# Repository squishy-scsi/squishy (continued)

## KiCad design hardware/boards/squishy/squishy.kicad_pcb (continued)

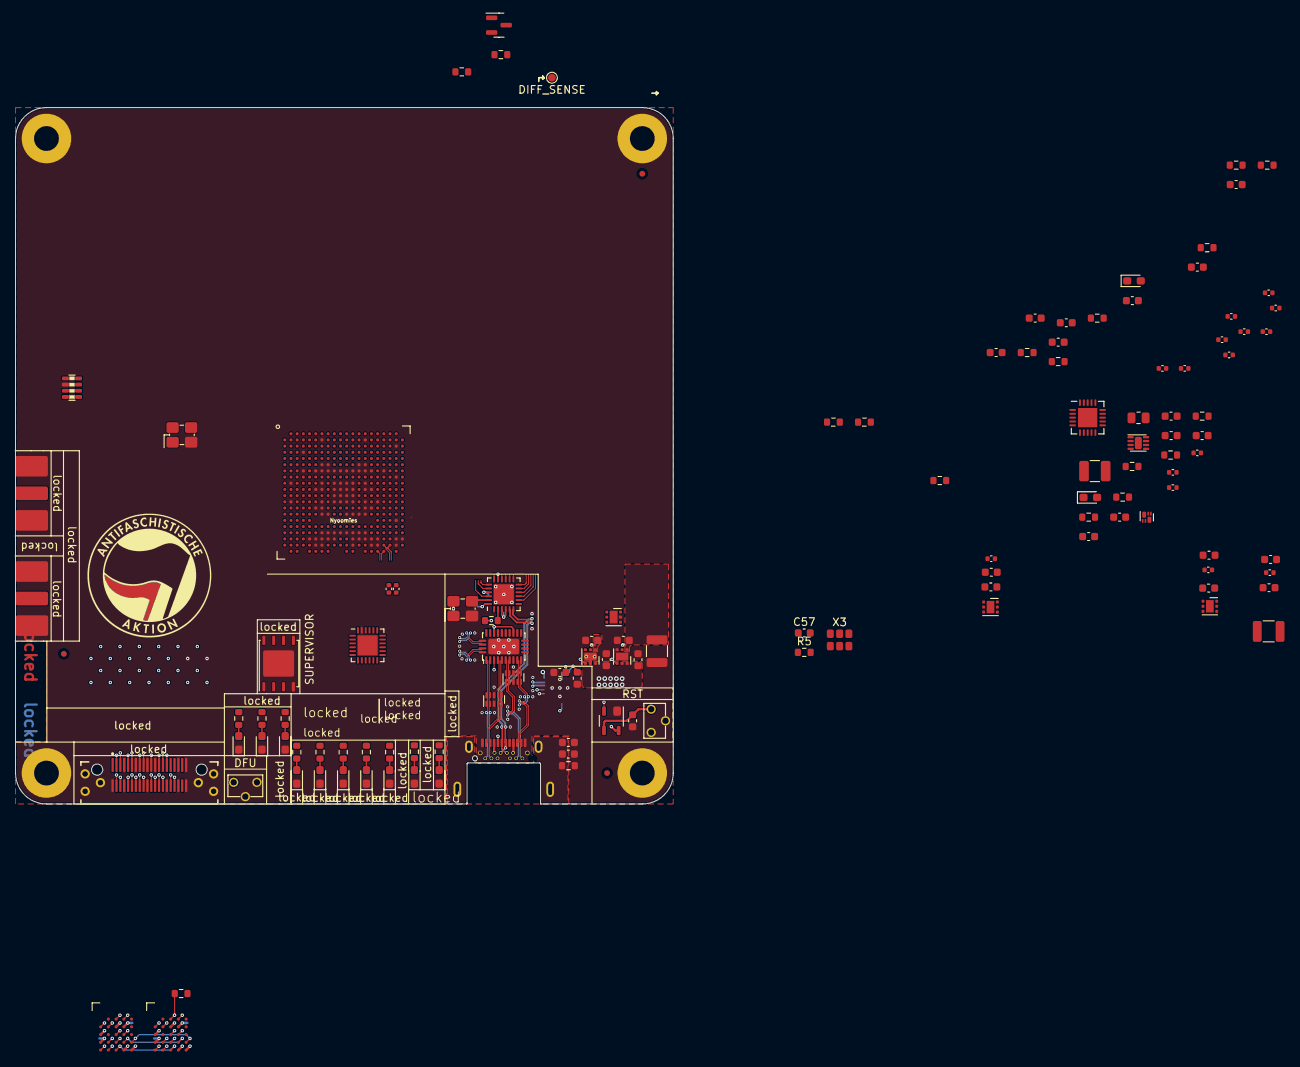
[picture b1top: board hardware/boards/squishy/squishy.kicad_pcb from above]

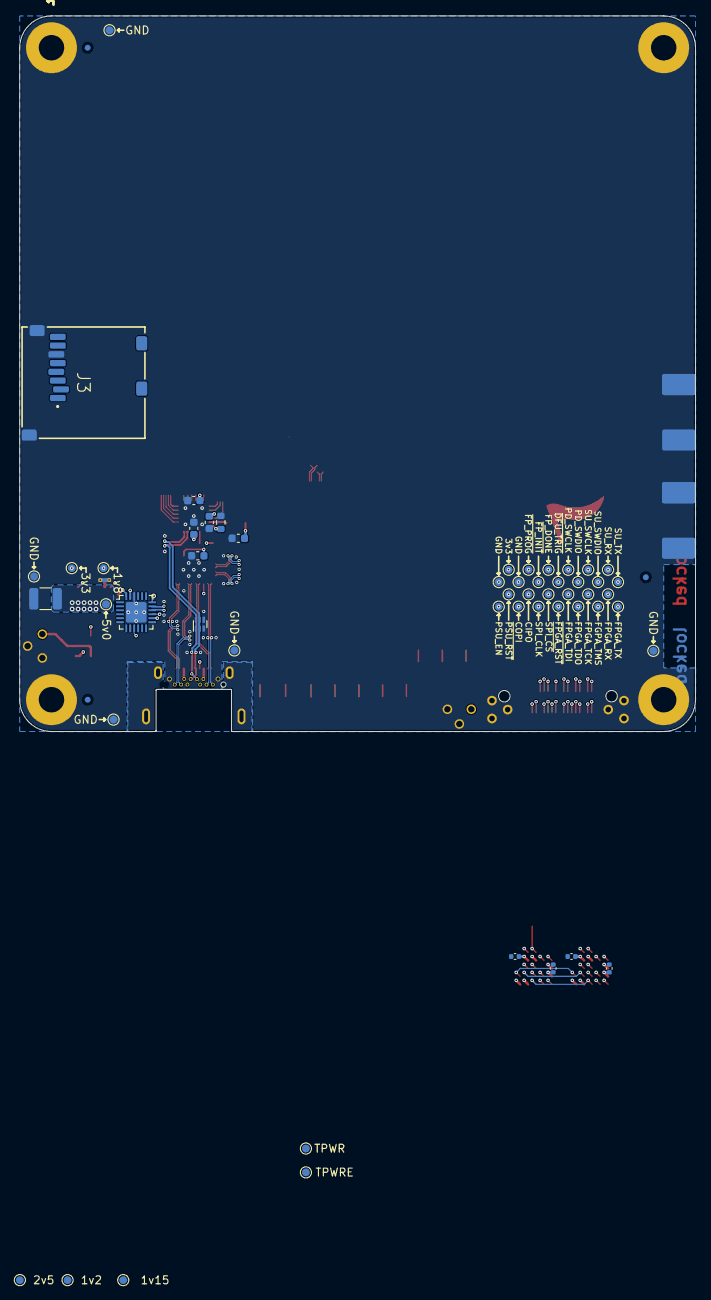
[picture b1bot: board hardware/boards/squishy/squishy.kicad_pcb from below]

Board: 6 copper layers, 85.0 x 90.0 mm, 186 parts (56 on the bottom side), 121 nets.

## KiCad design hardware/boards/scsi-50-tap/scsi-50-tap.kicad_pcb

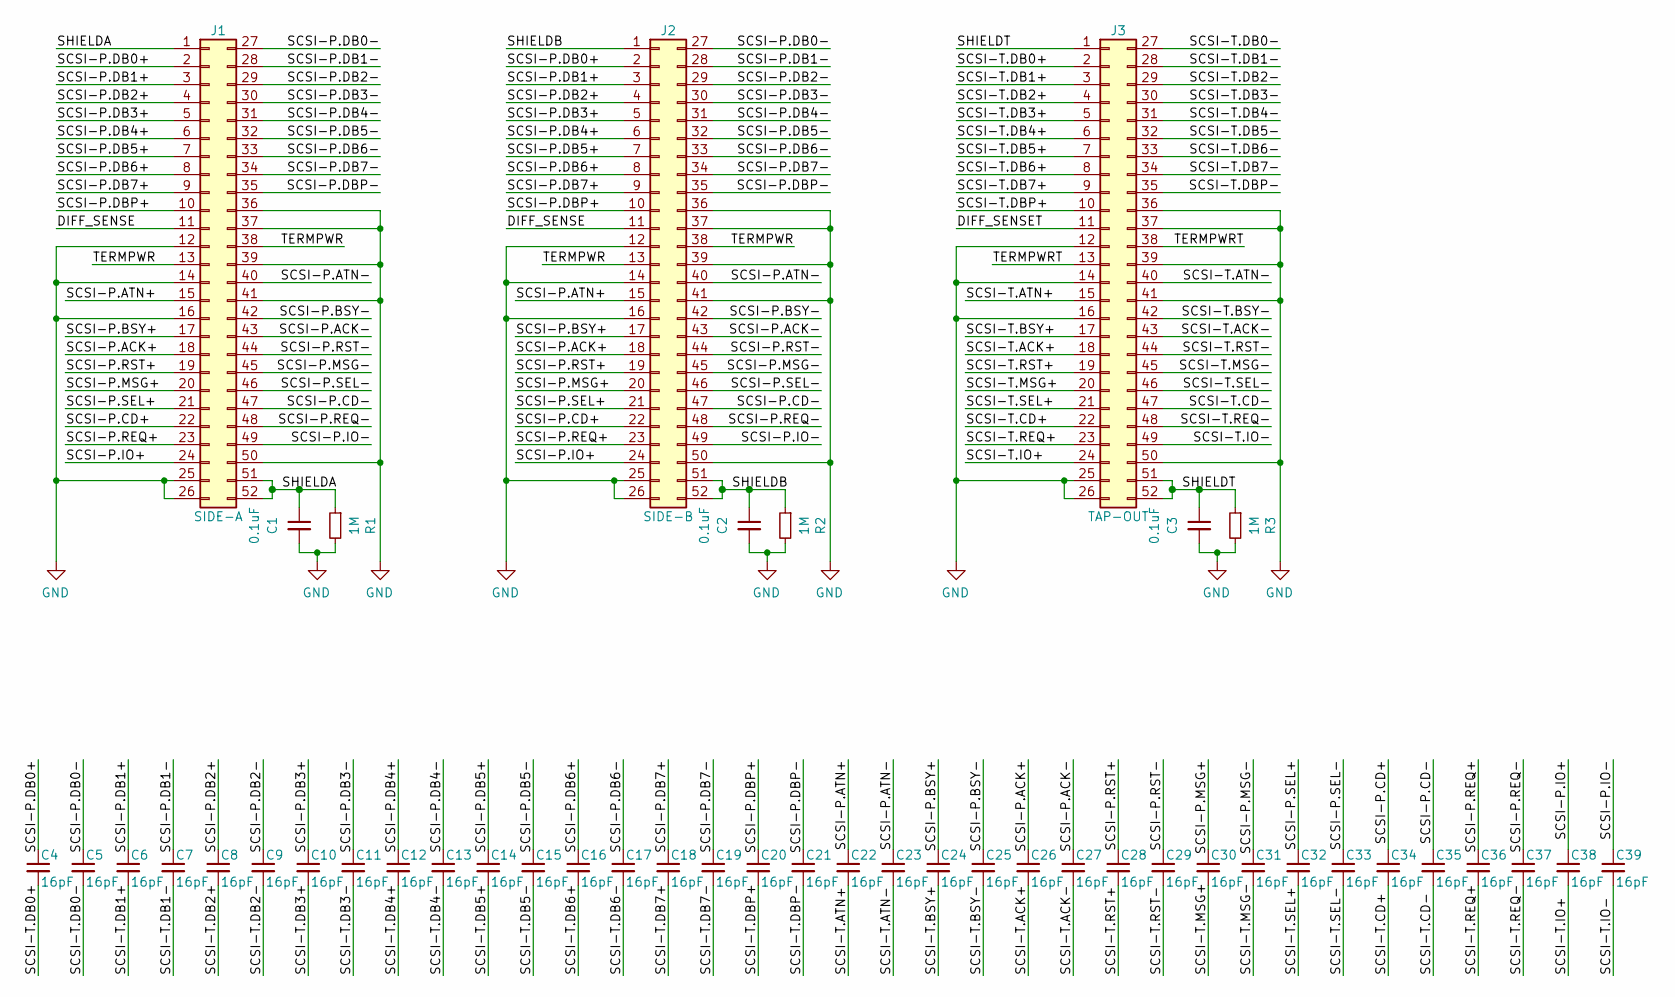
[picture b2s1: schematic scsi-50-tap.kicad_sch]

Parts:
C1, C2, C3: 0.1uF; C_0603_1608Metric; MPN C0603C104M5RACTU
C4, C5, C6, C7, C8, C9, C10, C11, C12, C13, C14, C15, C16, C17, C18, C19, C20, C21, C22, C23, C24, C25, C26, C27, C28, C29, C30, C31, C32, C33, C34, C35, C36, C37, C38, C39: 16pF; C_0402_1005Metric; Tolerance <=±2%; Voltage >=50V; MPN GRM1555C1H160GA01D
J1: SIDE-A; SCSI-50-PIN; MPN 112-050-213R491
J2: SIDE-B; SCSI-50-PIN; MPN 112-050-213R491
J3: TAP-OUT; SCSI-50-PIN; MPN 112-050-213R491
R1, R2, R3: 1M; R_0603_1608Metric; MPN CRCW06031M00FKEA

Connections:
/DIFF_SENSE: J1.11, J2.11
/DIFF_SENSET: J3.11
/SCSI-P.ACK+: C26.1, J1.18, J2.18
/SCSI-P.ACK-: C27.1, J1.43, J2.43
/SCSI-P.ATN+: C22.1, J1.15, J2.15
/SCSI-P.ATN-: C23.1, J1.40, J2.40
/SCSI-P.BSY+: C24.1, J1.17, J2.17
/SCSI-P.BSY-: C25.1, J1.42, J2.42
/SCSI-P.CD+: C34.1, J1.22, J2.22
/SCSI-P.CD-: C35.1, J1.47, J2.47
/SCSI-P.DB0+: C4.1, J1.2, J2.2
/SCSI-P.DB0-: C5.1, J1.27, J2.27
/SCSI-P.DB1+: C6.1, J1.3, J2.3
/SCSI-P.DB1-: C7.1, J1.28, J2.28
/SCSI-P.DB2+: C8.1, J1.4, J2.4
/SCSI-P.DB2-: C9.1, J1.29, J2.29
/SCSI-P.DB3+: C10.1, J1.5, J2.5
/SCSI-P.DB3-: C11.1, J1.30, J2.30
/SCSI-P.DB4+: C12.1, J1.6, J2.6
/SCSI-P.DB4-: C13.1, J1.31, J2.31
/SCSI-P.DB5+: C14.1, J1.7, J2.7
/SCSI-P.DB5-: C15.1, J1.32, J2.32
/SCSI-P.DB6+: C16.1, J1.8, J2.8
/SCSI-P.DB6-: C17.1, J1.33, J2.33
/SCSI-P.DB7+: C18.1, J1.9, J2.9
/SCSI-P.DB7-: C19.1, J1.34, J2.34
/SCSI-P.DBP+: C20.1, J1.10, J2.10
/SCSI-P.DBP-: C21.1, J1.35, J2.35
/SCSI-P.IO+: C38.1, J1.24, J2.24
/SCSI-P.IO-: C39.1, J1.49, J2.49
/SCSI-P.MSG+: C30.1, J1.20, J2.20
/SCSI-P.MSG-: C31.1, J1.45, J2.45
/SCSI-P.REQ+: C36.1, J1.23, J2.23
/SCSI-P.REQ-: C37.1, J1.48, J2.48
/SCSI-P.RST+: C28.1, J1.19, J2.19
/SCSI-P.RST-: C29.1, J1.44, J2.44
/SCSI-P.SEL+: C32.1, J1.21, J2.21
/SCSI-P.SEL-: C33.1, J1.46, J2.46
/SCSI-T.ACK+: C26.2, J3.18
/SCSI-T.ACK-: C27.2, J3.43
/SCSI-T.ATN+: C22.2, J3.15
/SCSI-T.ATN-: C23.2, J3.40
/SCSI-T.BSY+: C24.2, J3.17
/SCSI-T.BSY-: C25.2, J3.42
/SCSI-T.CD+: C34.2, J3.22
/SCSI-T.CD-: C35.2, J3.47
/SCSI-T.DB0+: C4.2, J3.2
/SCSI-T.DB0-: C5.2, J3.27
/SCSI-T.DB1+: C6.2, J3.3
/SCSI-T.DB1-: C7.2, J3.28
/SCSI-T.DB2+: C8.2, J3.4
/SCSI-T.DB2-: C9.2, J3.29
/SCSI-T.DB3+: C10.2, J3.5
/SCSI-T.DB3-: C11.2, J3.30
/SCSI-T.DB4+: C12.2, J3.6
/SCSI-T.DB4-: C13.2, J3.31
/SCSI-T.DB5+: C14.2, J3.7
/SCSI-T.DB5-: C15.2, J3.32
/SCSI-T.DB6+: C16.2, J3.8
/SCSI-T.DB6-: C17.2, J3.33
/SCSI-T.DB7+: C18.2, J3.9
/SCSI-T.DB7-: C19.2, J3.34
/SCSI-T.DBP+: C20.2, J3.10
/SCSI-T.DBP-: C21.2, J3.35
/SCSI-T.IO+: C38.2, J3.24
/SCSI-T.IO-: C39.2, J3.49
/SCSI-T.MSG+: C30.2, J3.20
/SCSI-T.MSG-: C31.2, J3.45
/SCSI-T.REQ+: C36.2, J3.23
/SCSI-T.REQ-: C37.2, J3.48
/SCSI-T.RST+: C28.2, J3.19
/SCSI-T.RST-: C29.2, J3.44
/SCSI-T.SEL+: C32.2, J3.21
/SCSI-T.SEL-: C33.2, J3.46
/SHIELDA: C1.1, J1.1, J1.51, J1.52, R1.1
/SHIELDB: C2.1, J2.1, J2.51, J2.52, R2.1
/SHIELDT: C3.1, J3.1, J3.51, J3.52, R3.1
/TERMPWR: J1.13, J1.38, J2.13, J2.38
/TERMPWRT: J3.13, J3.38
GND: C1.2, C2.2, C3.2, J1.12, J1.14, J1.16, J1.25, J1.26, J1.36, J1.37, J1.39, J1.41, J1.50, J2.12, J2.14, J2.16, J2.25, J2.26, J2.36, J2.37, J2.39, J2.41, J2.50, J3.12, J3.14, J3.16, J3.25, J3.26, J3.36, J3.37, J3.39, J3.41, J3.50, R1.2, R2.2, R3.2

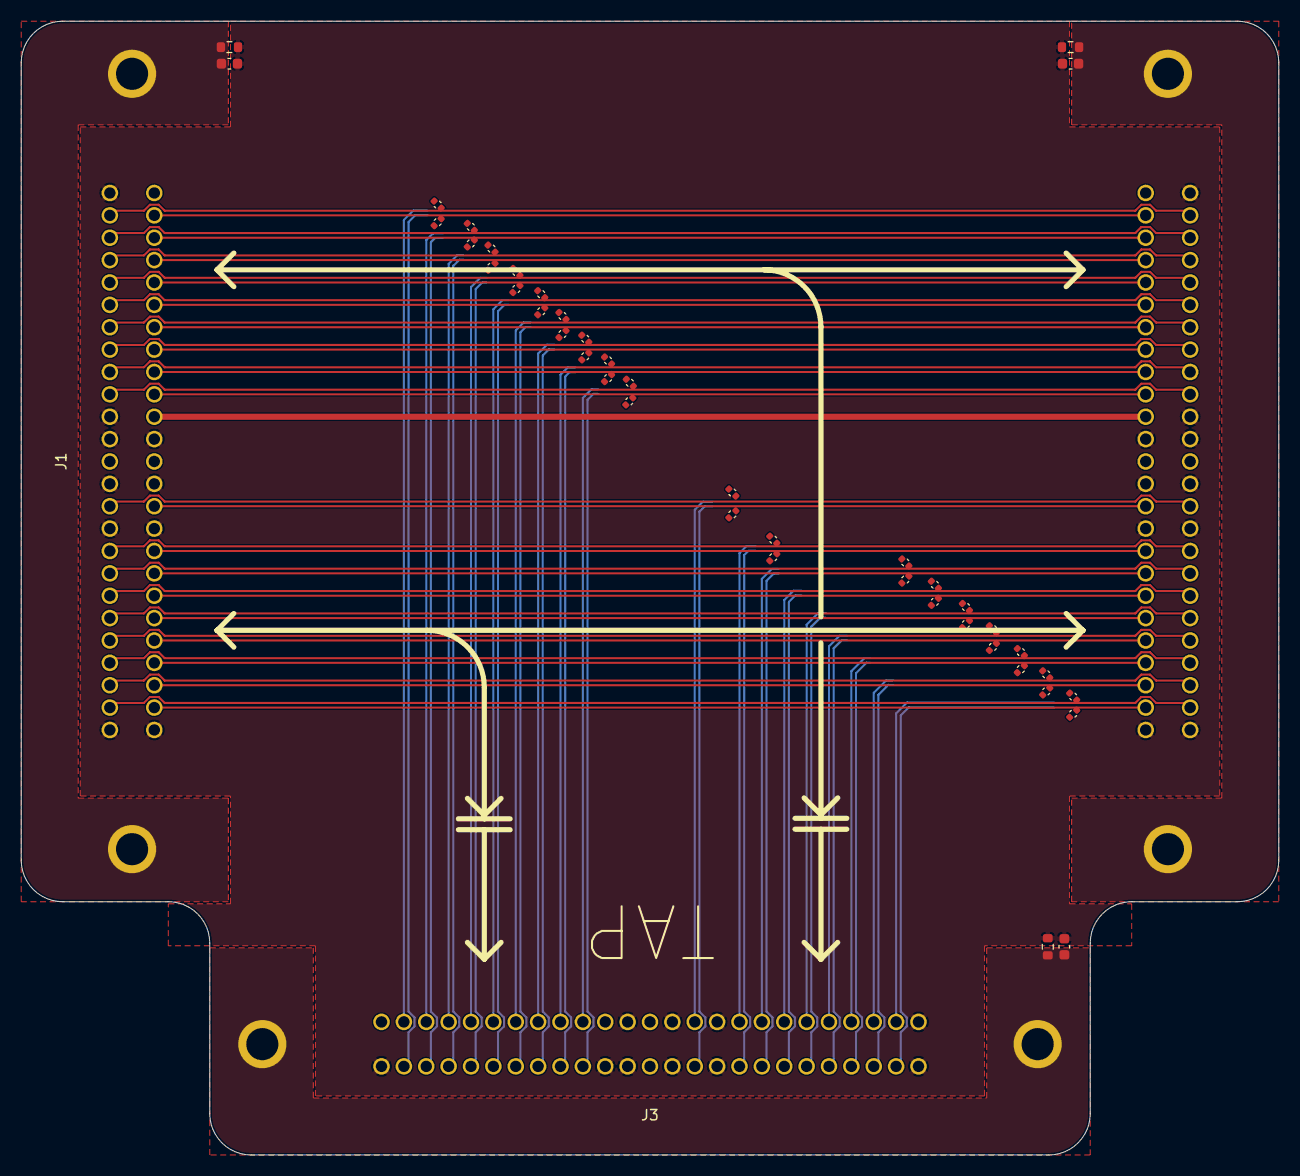
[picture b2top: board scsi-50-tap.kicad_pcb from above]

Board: 4 copper layers, 121.4 x 109.4 mm, 45 parts (1 on the bottom side), 79 nets.

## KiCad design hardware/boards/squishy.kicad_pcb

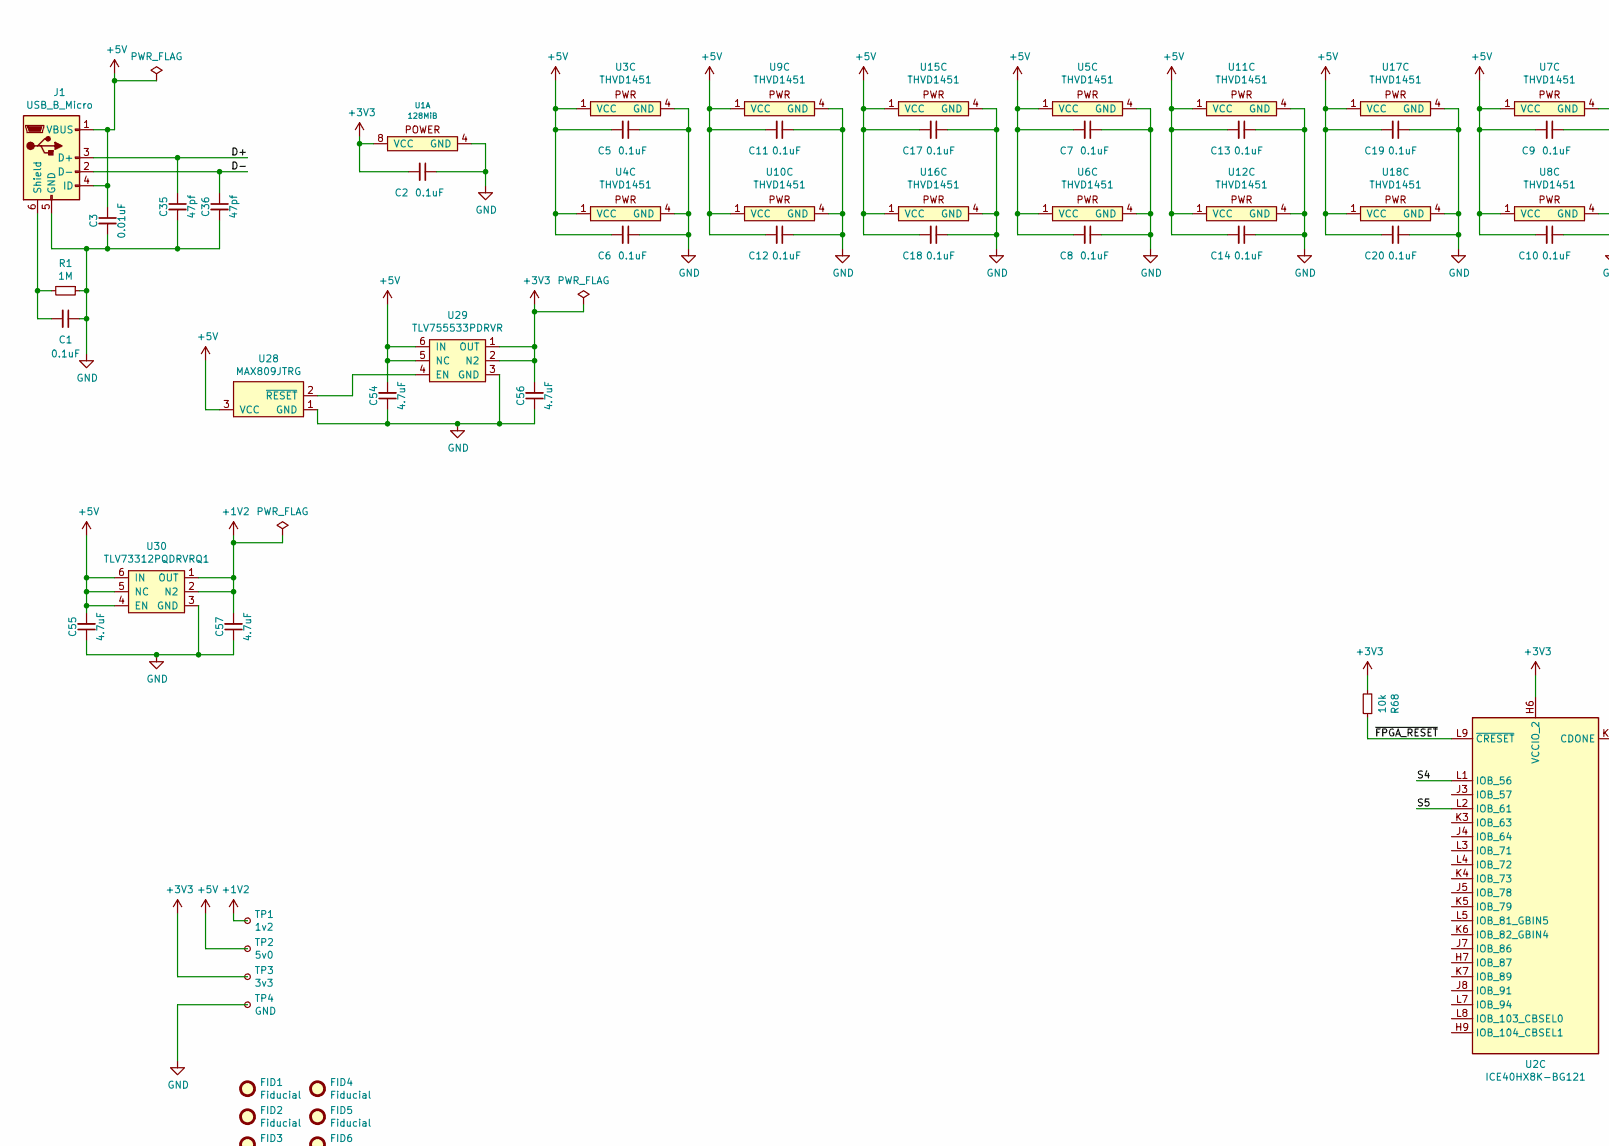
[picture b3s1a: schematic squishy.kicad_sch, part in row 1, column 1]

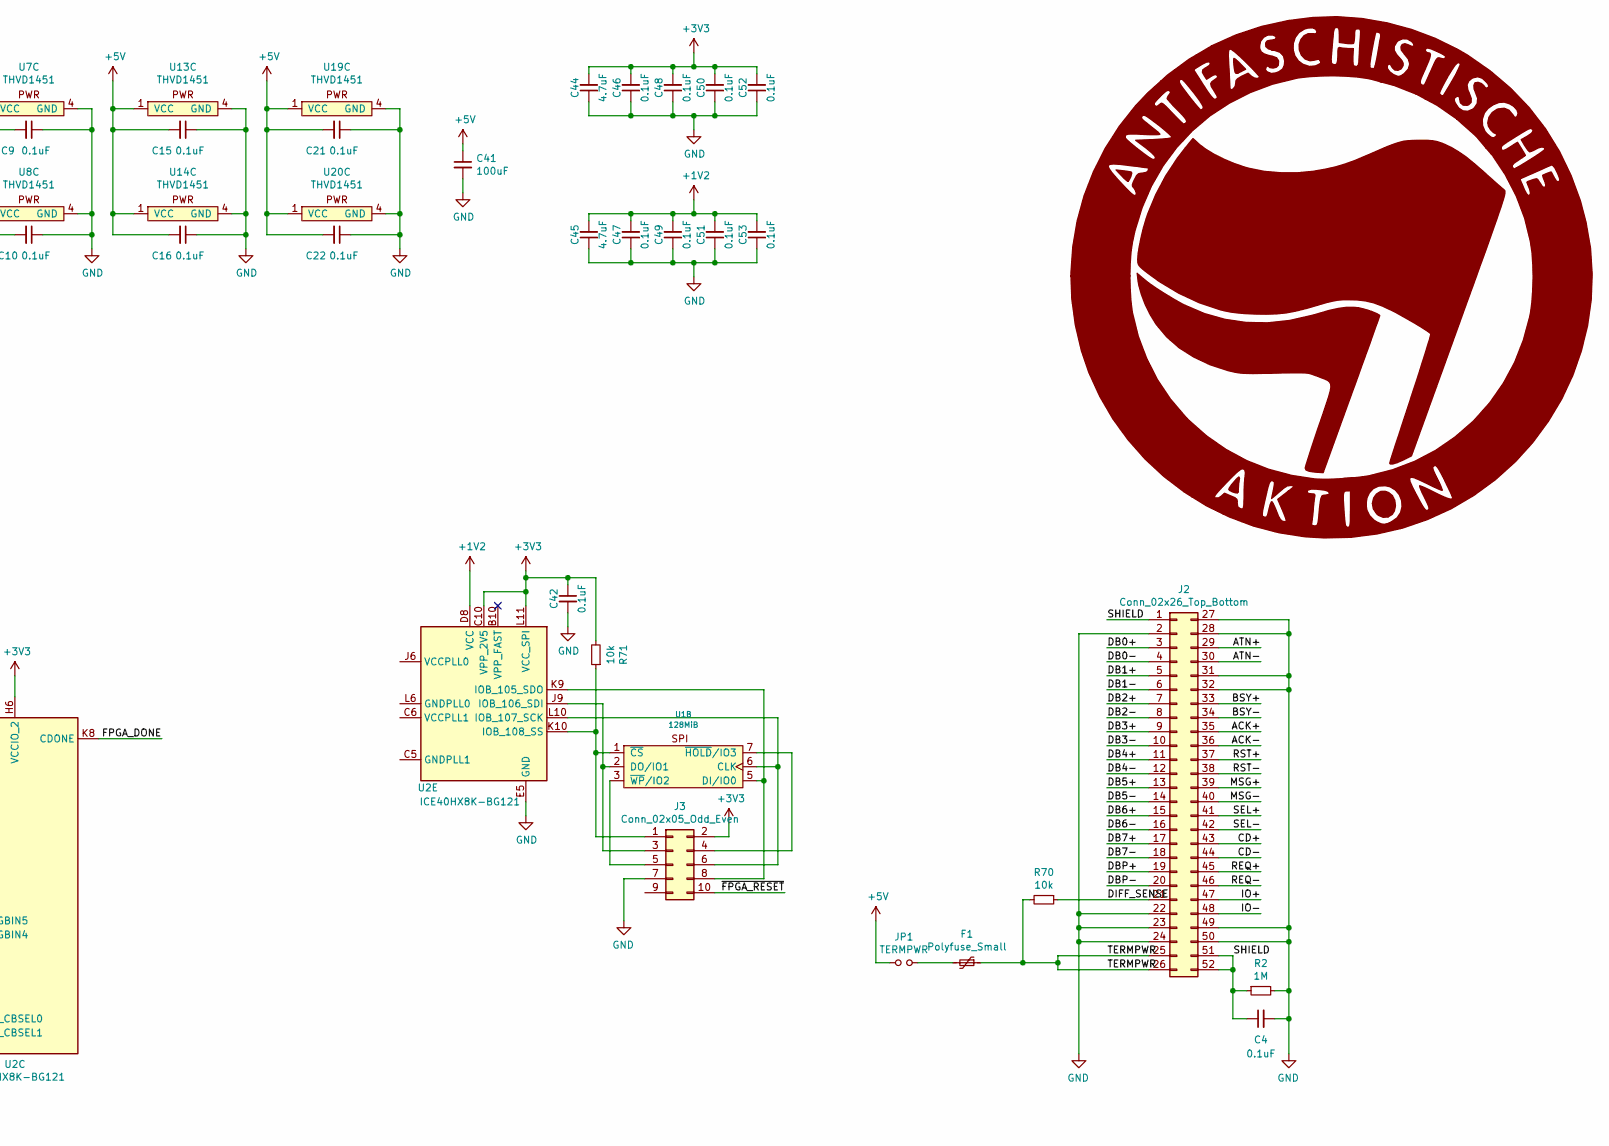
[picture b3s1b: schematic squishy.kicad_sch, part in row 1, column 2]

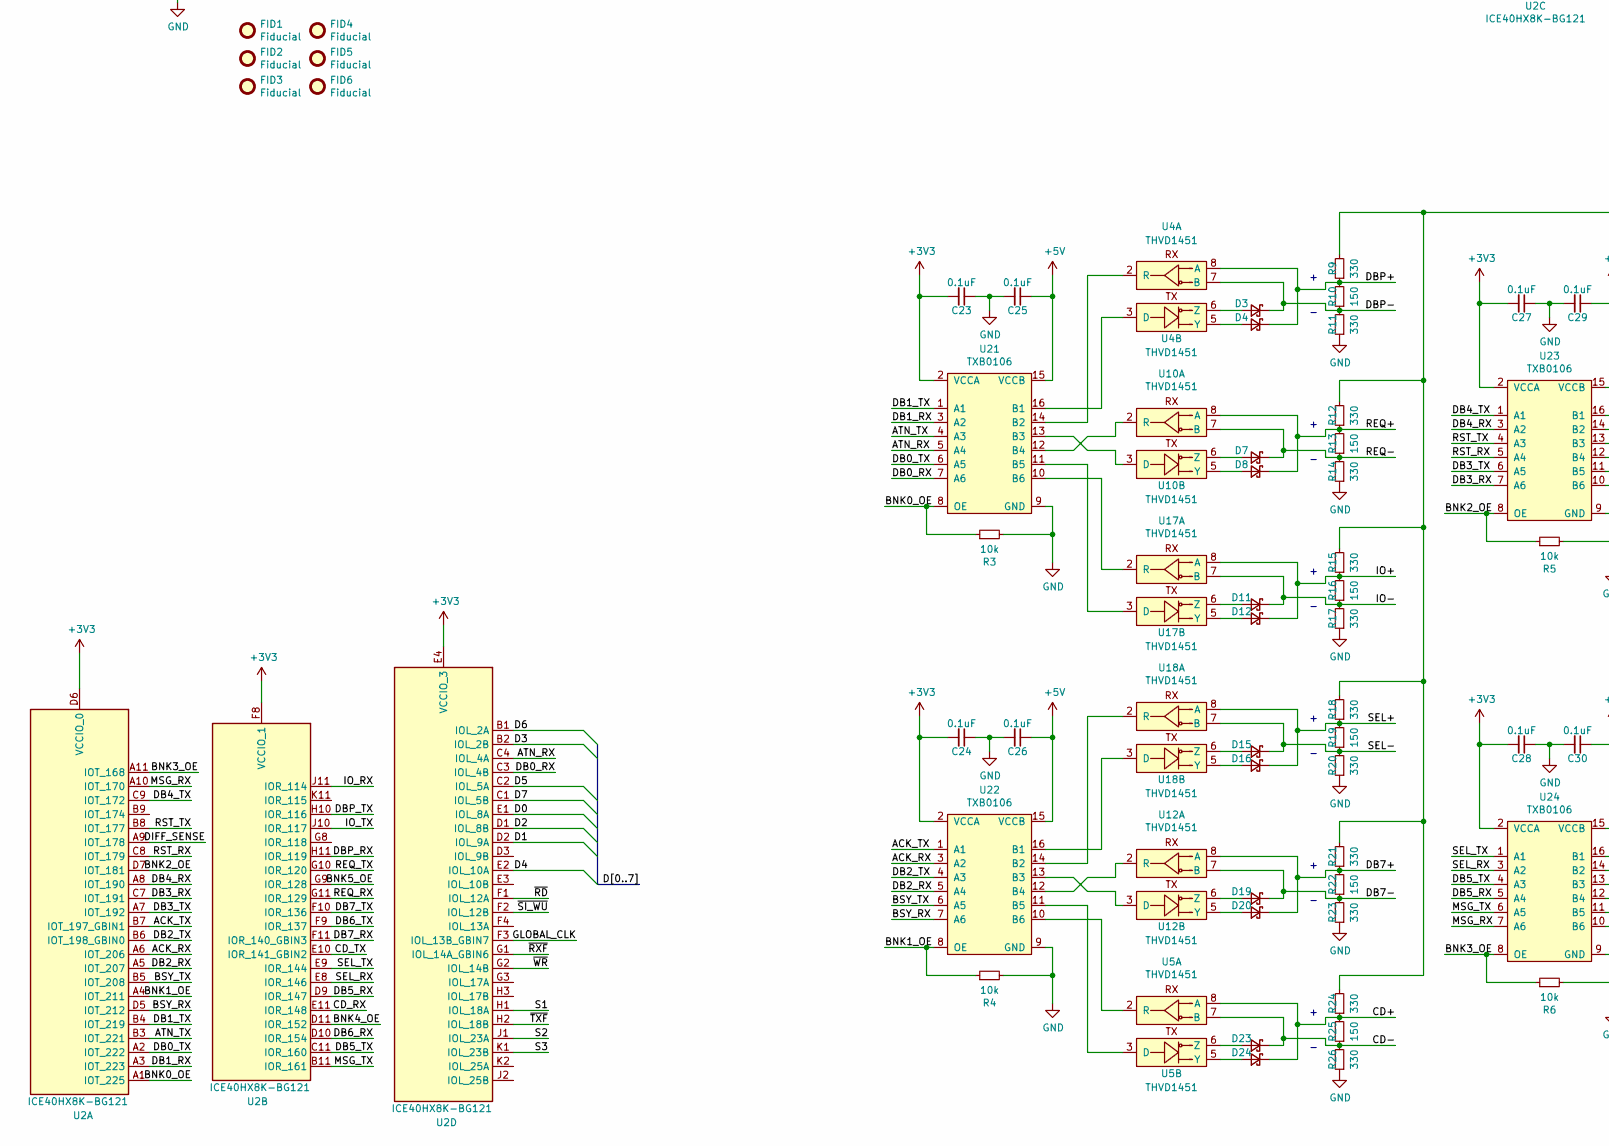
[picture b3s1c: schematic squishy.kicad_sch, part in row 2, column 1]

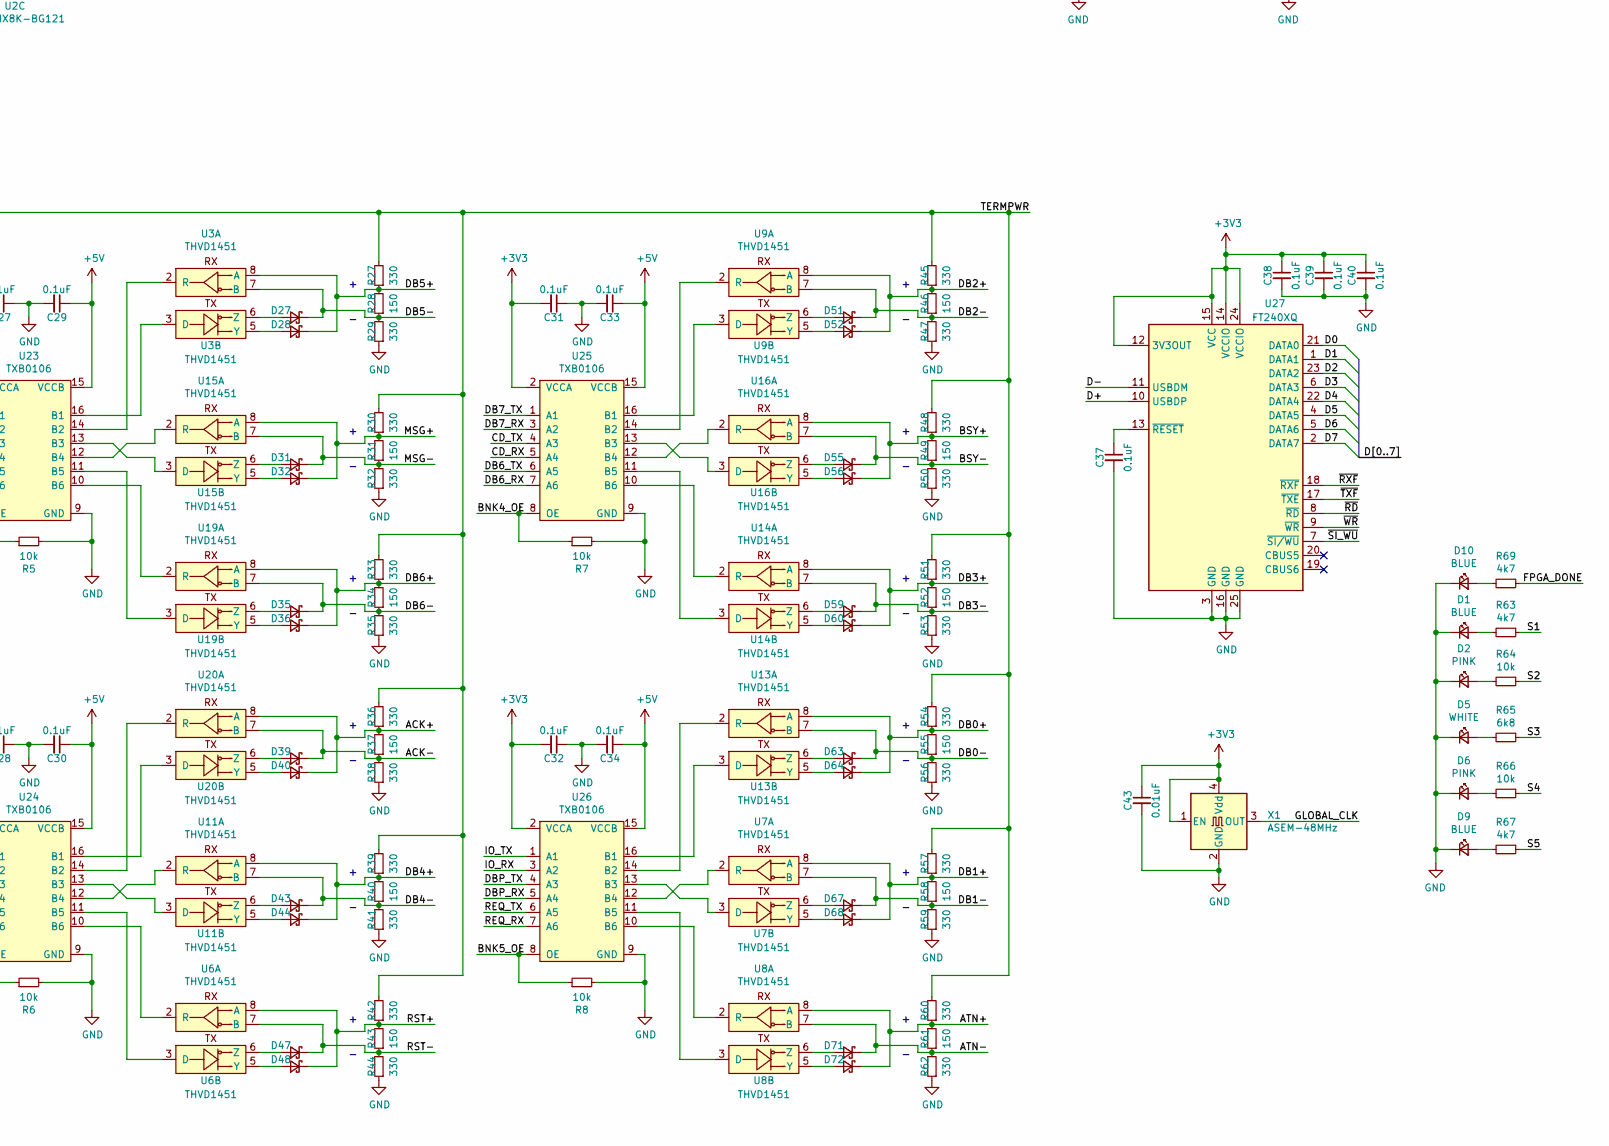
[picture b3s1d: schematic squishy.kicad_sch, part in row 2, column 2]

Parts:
C1, C4: 0.1uF; C_0603_1608Metric; MPN C0603C104M5RACTU
C2, C5, C6, C7, C8, C9, C10, C11, C12, C13, C14, C15, C16, C17, C18, C19, C20, C21, C22, C23, C24, C25, C26, C27, C28, C29, C30, C31, C32, C33, C34, C37, C38, C39, C40, C42, C46, C47, C48, C49, C50, C51, C52, C53: 0.1uF; C_0402_1005Metric; MPN C0402C104M8PACTU
C3, C43: 0.01uF; C_0402_1005Metric; MPN C0402C103K3RACTU
C35, C36: 47pf; C_0402_1005Metric; MPN C0402C470K5GACTU
C41: 100uF; C_1210_3225Metric; MPN C1210C107M4PAC7800
C44, C45, C54, C55, C56, C57: 4.7uF; C_0603_1608Metric; MPN C0603C475K8PACTU
D1, D9, D10: BLUE; LED_0603_1608Metric_Pad1.05x0.95mm_HandSolder; MPN 150060BS75000
D2, D6: PINK; LED_0603_1608Metric_Pad1.05x0.95mm_HandSolder; MPN OSK40603C1E
D3, D4, D7, D8, D11, D12, D15, D16, D19, D20, D23, D24, D27, D28, D31, D32, D35, D36, D39, D40, D43, D44, D47, D48, D51, D52, D55, D56, D59, D60, D63, D64, D67, D68, D71, D72: D_Schottky_Small; D_0402_1005Metric; MPN CDBQR0230L-HF
D5: WHITE; LED_0603_1608Metric_Pad1.05x0.95mm_HandSolder; MPN SMLEN3WBC8W1
F1: Polyfuse_Small; Fuse_1210_3225Metric_Castellated; MPN 0ZCH0050FF2G
FID1, FID2, FID3, FID4, FID5, FID6: Fiducial; Fiducial_0.75mm_Mask1.5mm
G1: Antifaschistische_Aktion; Antifaschistische Aktion_600dpi
J1: USB_B_Micro; MICRO-USB-B-(IN_PCB); MPN 10103593-0001lf
J2: Conn_02x26_Top_Bottom; SCSI-50-PIN; MPN 112-050-113R001
J3: Conn_02x05_Odd_Even; FTSH-105-01-L-DV-K-TR; MPN FTSH-105-01-L-DV-K-TR
JP1: TERMPWR; PinHeader_1x02_P2.54mm_Vertical
R1, R2: 1M; R_0603_1608Metric; MPN CRCW06031M00FKEA
R3, R4, R5, R6, R7, R8, R64, R66, R68, R70, R71: 10k; R_0603_1608Metric; MPN CRCW060310K0FKEA
R9, R11, R12, R14, R15, R17, R18, R20, R21, R23, R24, R26, R27, R29, R30, R32, R33, R35, R36, R38, R39, R41, R42, R44, R45, R47, R48, R50, R51, R53, R54, R56, R57, R59, R60, R62: 330; R_0402_1005Metric; MPN CRGCQ0402F330R
R10, R13, R16, R19, R22, R25, R28, R31, R34, R37, R40, R43, R46, R49, R52, R55, R58, R61: 150; R_0402_1005Metric; MPN CRGCQ0402F150R
R63, R67, R69: 4k7; R_0603_1608Metric; MPN CRCW06034K70FKEA
R65: 6k8; R_0603_1608Metric; MPN CRCW06036K80FKEA
TP1: 1v2; TestPoint_Pad_D1.0mm
TP2: 5v0; TestPoint_Pad_D1.0mm
TP3: 3v3; TestPoint_Pad_D1.0mm
TP4: GND; TestPoint_Pad_D1.0mm
U1: 128MiB; WSON-8-1EP-6.0x8.0mm; MPN W25N01GVZEIG TR
U2: ICE40HX8K-BG121; BGA-121_9.0x9.0mm_Layout11x11_P0.8mm_Ball0.4mm_Pad0.35mm_NS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; MPN ICE40HX8K-BG121
U3, U4, U5, U6, U7, U8, U9, U10, U11, U12, U13, U14, U15, U16, U17, U18, U19, U20: THVD1451; VSON_8_3mm_x_3mm_1EP; MPN THVD1451DRBR
U21, U22, U23, U24, U25, U26: TXB0106; R-PVQFN-N16; MPN TXB0106RGYR
U27: FT240XQ; QFN-24-1EP_4x4mm_P0.5mm_EP2.6x2.6mm; MPN FT240XQ-R
U28: MAX809JTRG; SOT-23; MPN MAX809JTRG
U29: TLV755533PDRVR; DFN-6-1EP_2x2mm_P0.65mm_EP1x1.6mm; MPN TLV75533PDRVR
U30: TLV73312PQDRVRQ1; DFN-6-1EP_2x2mm_P0.65mm_EP1x1.6mm; MPN TLV73312PQDRVRQ1
X1: ASEM-48MHz; Oscillator_SMD_Abracon_ASE-4Pin_3.2x2.5mm; MPN ASEMB-48.000MHZ-LY-T

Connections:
+1V2: C45.2, C47.2, C49.2, C51.2, C53.2, C57.2, TP1.1, U2.D4 (VCC), U2.D8 (VCC), U2.H4 (VCC), U2.H8 (VCC), U30.1 (OUT), U30.2 (N2)
+3V3: C2.2, C23.2, C24.2, C27.2, C28.2, C31.2, C32.2, C38.1, C39.1, C40.1, C42.1, C43.1, C44.2, C46.2, C48.2, C50.2, C52.2, C56.2, J3.2, R68.2, R71.2, TP3.1, U1.8 (VCC), U2.C10 (VPP_2V5), U2.D6 (VCCIO_0), U2.E4 (VCCIO_3), U2.F8 (VCCIO_1), U2.G4 (VCCIO_3), U2.H6 (VCCIO_2), U2.L11 (VCC_SPI), U21.2 (VCCA), U22.2 (VCCA), U23.2 (VCCA), U24.2 (VCCA), U25.2 (VCCA), U26.2 (VCCA), U27.12 (3V3OUT), U27.14 (VCCIO), U27.15 (VCC), U27.24 (VCCIO), U29.1 (OUT), U29.2 (N2), X1.1 (EN), X1.4 (Vdd)
+5V: C3.1, C5.2, C6.2, C7.2, C8.2, C9.2, C10.2, C11.2, C12.2, C13.2, C14.2, C15.2, C16.2, C17.2, C18.2, C19.2, C20.2, C21.2, C22.2, C25.1, C26.1, C29.1, C30.1, C33.1, C34.1, C41.1, C54.2, C55.2, J1.1 (VBUS), J1.4 (ID), JP1.1, TP2.1, U3.1 (VCC), U4.1 (VCC), U5.1 (VCC), U6.1 (VCC), U7.1 (VCC), U8.1 (VCC), U9.1 (VCC), U10.1 (VCC), U11.1 (VCC), U12.1 (VCC), U13.1 (VCC), U14.1 (VCC), U15.1 (VCC), U16.1 (VCC), U17.1 (VCC), U18.1 (VCC), U19.1 (VCC), U20.1 (VCC), U21.15 (VCCB), U22.15 (VCCB), U23.15 (VCCB), U24.15 (VCCB), U25.15 (VCCB), U26.15 (VCCB), U28.3 (VCC), U29.5 (NC), U29.6 (IN), U30.4 (EN), U30.5 (NC), U30.6 (IN)
/ACK+: D40.1 (K), J2.35, R36.1, R37.2, U20.8 (A)
/ACK-: D39.1 (K), J2.36, R37.1, R38.2, U20.7 (B)
/ACK_RX: U2.A6 (IOT_206), U22.3 (A2)
/ACK_TX: U2.B7 (IOT_197_GBIN1), U22.1 (A1)
/ATN+: D72.1 (K), J2.29, R60.1, R61.2, U8.8 (A)
/ATN-: D71.1 (K), J2.30, R61.1, R62.2, U8.7 (B)
/ATN_RX: U2.C4 (IOL_4A), U21.5 (A4)
/ATN_TX: U2.B3 (IOT_221), U21.4 (A3)
/BNK0_OE: R3.1, U2.A1 (IOT_225), U21.8 (OE)
/BNK1_OE: R4.1, U2.A4 (IOT_211), U22.8 (OE)
/BNK2_OE: R5.1, U2.D7 (IOT_181), U23.8 (OE)
/BNK3_OE: R6.1, U2.A11 (IOT_168), U24.8 (OE)
/BNK4_OE: R7.1, U2.D11 (IOR_152), U25.8 (OE)
/BNK5_OE: R8.1, U2.G9 (IOR_128), U26.8 (OE)
/BSY+: D56.1 (K), J2.33, R48.1, R49.2, U16.8 (A)
/BSY-: D55.1 (K), J2.34, R49.1, R50.2, U16.7 (B)
/BSY_RX: U2.D5 (IOT_212), U22.7 (A6)
/BSY_TX: U2.B5 (IOT_208), U22.6 (A5)
/CD+: D24.1 (K), J2.43, R24.1, R25.2, U5.8 (A)
/CD-: D23.1 (K), J2.44, R25.1, R26.2, U5.7 (B)
/CD_RX: U2.E11 (IOR_148), U25.5 (A4)
/CD_TX: U2.E10 (IOR_141_GBIN2), U25.4 (A3)
/D0: U2.E1 (IOL_8A), U27.21 (DATA0)
/D1: U2.D2 (IOL_9A), U27.1 (DATA1)
/D2: U2.D1 (IOL_8B), U27.23 (DATA2)
/D3: U2.B2 (IOL_2B), U27.6 (DATA3)
/D4: U2.E2 (IOL_10A), U27.22 (DATA4)
/D5: U2.C2 (IOL_5A), U27.4 (DATA5)
/D6: U2.B1 (IOL_2A), U27.5 (DATA6)
/D7: U2.C1 (IOL_5B), U27.2 (DATA7)
/D+: C35.1, J1.3 (D+), U27.10 (USBDP)
/D-: C36.1, J1.2 (D-), U27.11 (USBDM)
/DB0+: D64.1 (K), J2.3, R54.1, R55.2, U13.8 (A)
/DB0-: D63.1 (K), J2.4, R55.1, R56.2, U13.7 (B)
/DB0_RX: U2.C3 (IOL_4B), U21.7 (A6)
/DB0_TX: U2.A2 (IOT_222), U21.6 (A5)
/DB1+: D68.1 (K), J2.5, R57.1, R58.2, U7.8 (A)
/DB1-: D67.1 (K), J2.6, R58.1, R59.2, U7.7 (B)
/DB1_RX: U2.A3 (IOT_223), U21.3 (A2)
/DB1_TX: U2.B4 (IOT_219), U21.1 (A1)
/DB2+: D52.1 (K), J2.7, R45.1, R46.2, U9.8 (A)
/DB2-: D51.1 (K), J2.8, R46.1, R47.2, U9.7 (B)
/DB2_RX: U2.A5 (IOT_207), U22.5 (A4)
/DB2_TX: U2.B6 (IOT_198_GBIN0), U22.4 (A3)
/DB3+: D60.1 (K), J2.9, R51.1, R52.2, U14.8 (A)
/DB3-: D59.1 (K), J2.10, R52.1, R53.2, U14.7 (B)
/DB3_RX: U2.C7 (IOT_191), U23.7 (A6)
/DB3_TX: U2.A7 (IOT_192), U23.6 (A5)
/DB4+: D44.1 (K), J2.11, R39.1, R40.2, U11.8 (A)
/DB4-: D43.1 (K), J2.12, R40.1, R41.2, U11.7 (B)
/DB4_RX: U2.A8 (IOT_190), U23.3 (A2)
/DB4_TX: U2.C9 (IOT_172), U23.1 (A1)
/DB5+: D28.1 (K), J2.13, R27.1, R28.2, U3.8 (A)
/DB5-: D27.1 (K), J2.14, R28.1, R29.2, U3.7 (B)
/DB5_RX: U2.D9 (IOR_147), U24.5 (A4)
/DB5_TX: U2.C11 (IOR_160), U24.4 (A3)
/DB6+: D36.1 (K), J2.15, R33.1, R34.2, U19.8 (A)
/DB6-: D35.1 (K), J2.16, R34.1, R35.2, U19.7 (B)
/DB6_RX: U2.D10 (IOR_154), U25.7 (A6)
/DB6_TX: U2.F9 (IOR_137), U25.6 (A5)
/DB7+: D20.1 (K), J2.17, R21.1, R22.2, U12.8 (A)
/DB7-: D19.1 (K), J2.18, R22.1, R23.2, U12.7 (B)
/DB7_RX: U2.F11 (IOR_140_GBIN3), U25.3 (A2)
/DB7_TX: U2.F10 (IOR_136), U25.1 (A1)
/DBP+: D4.1 (K), J2.19, R9.1, R10.2, U4.8 (A)
/DBP-: D3.1 (K), J2.20, R10.1, R11.2, U4.7 (B)
/DBP_RX: U2.H11 (IOR_119), U26.5 (A4)
/DBP_TX: U2.H10 (IOR_116), U26.4 (A3)
/DIFF_SENSE: J2.21, R70.1, U2.A9 (IOT_178)
/FPGA_DONE: R69.1, U2.K8 (CDONE)
/GLOBAL_CLK: U2.F3 (IOL_13B_GBIN7), X1.3 (OUT)
/IO+: D12.1 (K), J2.47, R15.1, R16.2, U17.8 (A)
/IO-: D11.1 (K), J2.48, R16.1, R17.2, U17.7 (B)
/IO_RX: U2.J11 (IOR_114), U26.3 (A2)
/IO_TX: U2.J10 (IOR_117), U26.1 (A1)
/MSG+: D32.1 (K), J2.39, R30.1, R31.2, U15.8 (A)
/MSG-: D31.1 (K), J2.40, R31.1, R32.2, U15.7 (B)
/MSG_RX: U2.A10 (IOT_170), U24.7 (A6)
/MSG_TX: U2.B11 (IOR_161), U24.6 (A5)
/REQ+: D8.1 (K), J2.45, R12.1, R13.2, U10.8 (A)
/REQ-: D7.1 (K), J2.46, R13.1, R14.2, U10.7 (B)
/REQ_RX: U2.G11 (IOR_129), U26.7 (A6)
/REQ_TX: U2.G10 (IOR_120), U26.6 (A5)
/RST+: D48.1 (K), J2.37, R42.1, R43.2, U6.8 (A)
/RST-: D47.1 (K), J2.38, R43.1, R44.2, U6.7 (B)
/RST_RX: U2.C8 (IOT_179), U23.5 (A4)
/RST_TX: U2.B8 (IOT_177), U23.4 (A3)
/S1: R63.1, U2.H1 (IOL_18A)
/S2: R64.1, U2.J1 (IOL_23A)
/S3: R65.1, U2.K1 (IOL_23B)
/S4: R66.1, U2.L1 (IOB_56)
/S5: R67.1, U2.L2 (IOB_61)
/SEL+: D16.1 (K), J2.41, R18.1, R19.2, U18.8 (A)
/SEL-: D15.1 (K), J2.42, R19.1, R20.2, U18.7 (B)
/SEL_RX: U2.E8 (IOR_146), U24.3 (A2)
/SEL_TX: U2.E9 (IOR_144), U24.1 (A1)
/SHIELD: C4.1, J2.1, J2.51, J2.52, R2.1
/TERMPWR: F1.1, J2.25, J2.26, R9.2, R12.2, R15.2, R18.2, R21.2, R24.2, R27.2, R30.2, R33.2, R36.2, R39.2, R42.2, R45.2, R48.2, R51.2, R54.2, R57.2, R60.2, R70.2
/~FPGA_RESET: J3.10, R68.1, U2.L9 (~CRESET)
/~RD: U2.F1 (IOL_12A), U27.8 (~RD)
/~RXF: U2.G1 (IOL_14A_GBIN6), U27.18 (~RXF)
/~SI_WU: U2.F2 (IOL_12B), U27.7 (~SI/WU)
/~TXF: U2.H2 (IOL_18B), U27.17 (~TXE)
/~WR: U2.G2 (IOL_14B), U27.9 (~WR)
GND: C1.1, C2.1, C3.2, C4.2, C5.1, C6.1, C7.1, C8.1, C9.1, C10.1, C11.1, C12.1, C13.1, C14.1, C15.1, C16.1, C17.1, C18.1, C19.1, C20.1, C21.1, C22.1, C23.1, C24.1, C25.2, C26.2, C27.1, C28.1, C29.2, C30.2, C31.1, C32.1, C33.2, C34.2, C35.2, C36.2, C37.2, C38.2, C39.2, C40.2, C41.2, C42.2, C43.2, C44.1, C45.1, C46.1, C47.1, C48.1, C49.1, C50.1, C51.1, C52.1, C53.1, C54.1, C55.1, C56.1, C57.1, D1.1 (K), D2.1 (K), D5.1 (K), D6.1 (K), D9.1 (K), D10.1 (K), J1.5 (GND), J2.2, J2.22, J2.23, J2.24, J2.27, J2.28, J2.31, J2.32, J2.49, J2.50, J3.7, R1.1, R2.2, R3.2, R4.2, R5.2, R6.2, R7.2, R8.2, R11.1, R14.1, R17.1, R20.1, R23.1, R26.1, R29.1, R32.1, R35.1, R38.1, R41.1, R44.1, R47.1, R50.1, R53.1, R56.1, R59.1, R62.1, TP4.1, U1.4 (GND), U1.9 (GND), U2.E5 (GND), U2.E6 (GND), U2.E7 (GND), U2.F5 (GND), U2.F6 (GND), U2.F7 (GND), U2.G5 (GND), U2.G6 (GND), U2.G7 (GND), U2.H5 (GND), U3.4 (GND), U3.9 (GND), U4.4 (GND), U4.9 (GND), U5.4 (GND), U5.9 (GND), U6.4 (GND), U6.9 (GND), U7.4 (GND), U7.9 (GND), U8.4 (GND), U8.9 (GND), U9.4 (GND), U9.9 (GND), U10.4 (GND), U10.9 (GND), U11.4 (GND), U11.9 (GND), U12.4 (GND), U12.9 (GND), U13.4 (GND), U13.9 (GND), U14.4 (GND), U14.9 (GND), U15.4 (GND), U15.9 (GND), U16.4 (GND), U16.9 (GND), U17.4 (GND), U17.9 (GND), U18.4 (GND), U18.9 (GND), U19.4 (GND), U19.9 (GND), U20.4 (GND), U20.9 (GND), U21.9 (GND), U21.17 (GND), U22.9 (GND), U22.17 (GND), U23.9 (GND), U23.17 (GND), U24.9 (GND), U24.17 (GND), U25.9 (GND), U25.17 (GND), U26.9 (GND), U26.17 (GND), U27.3 (GND), U27.16 (GND), U27.25 (GND), U28.1 (GND), U29.3 (GND), U29.7 (GND), U30.3 (GND), U30.7 (GND), X1.2 (GND)
unnamed: C1.2, J1.6 (Shield), R1.2
unnamed: C37.1, U27.13 (~RESET)
unnamed: D1.2 (A), R63.2
unnamed: D2.2 (A), R64.2
unnamed: D3.2 (A), U4.6 (Z)
unnamed: D4.2 (A), U4.5 (Y)
unnamed: D5.2 (A), R65.2
unnamed: D6.2 (A), R66.2
unnamed: D7.2 (A), U10.6 (Z)
unnamed: D8.2 (A), U10.5 (Y)
unnamed: D9.2 (A), R67.2
unnamed: D10.2 (A), R69.2
unnamed: D11.2 (A), U17.6 (Z)
unnamed: D12.2 (A), U17.5 (Y)
unnamed: D15.2 (A), U18.6 (Z)
unnamed: D16.2 (A), U18.5 (Y)
unnamed: D19.2 (A), U12.6 (Z)
unnamed: D20.2 (A), U12.5 (Y)
unnamed: D23.2 (A), U5.6 (Z)
unnamed: D24.2 (A), U5.5 (Y)
unnamed: D27.2 (A), U3.6 (Z)
unnamed: D28.2 (A), U3.5 (Y)
unnamed: D31.2 (A), U15.6 (Z)
unnamed: D32.2 (A), U15.5 (Y)
unnamed: D35.2 (A), U19.6 (Z)
unnamed: D36.2 (A), U19.5 (Y)
unnamed: D39.2 (A), U20.6 (Z)
unnamed: D40.2 (A), U20.5 (Y)
unnamed: D43.2 (A), U11.6 (Z)
unnamed: D44.2 (A), U11.5 (Y)
unnamed: D47.2 (A), U6.6 (Z)
unnamed: D48.2 (A), U6.5 (Y)
unnamed: D51.2 (A), U9.6 (Z)
unnamed: D52.2 (A), U9.5 (Y)
unnamed: D55.2 (A), U16.6 (Z)
unnamed: D56.2 (A), U16.5 (Y)
unnamed: D59.2 (A), U14.6 (Z)
unnamed: D60.2 (A), U14.5 (Y)
unnamed: D63.2 (A), U13.6 (Z)
unnamed: D64.2 (A), U13.5 (Y)
unnamed: D67.2 (A), U7.6 (Z)
unnamed: D68.2 (A), U7.5 (Y)
unnamed: D71.2 (A), U8.6 (Z)
unnamed: D72.2 (A), U8.5 (Y)
unnamed: F1.2, JP1.2
unnamed: J3.1, R71.1, U1.1 (~CS), U2.K10 (IOB_108_SS)
unnamed: J3.3, U1.2 (DO/IO1), U2.J9 (IOB_106_SDI)
unnamed: J3.4, U1.7 (~HOLD~/IO3)
unnamed: J3.5, U1.3 (~WP~/IO2)
unnamed: J3.6, U1.6 (CLK), U2.L10 (IOB_107_SCK)
unnamed: J3.8, U1.5 (DI/IO0), U2.K9 (IOB_105_SDO)
unnamed: U10.2 (R), U21.12 (B4)
unnamed: U10.3 (D), U21.13 (B3)
unnamed: U11.2 (R), U24.12 (B4)
unnamed: U11.3 (D), U24.13 (B3)
unnamed: U12.2 (R), U22.12 (B4)
unnamed: U12.3 (D), U22.13 (B3)
unnamed: U13.2 (R), U26.14 (B2)
unnamed: U13.3 (D), U26.16 (B1)
unnamed: U14.2 (R), U25.10 (B6)
unnamed: U14.3 (D), U25.11 (B5)
unnamed: U15.2 (R), U23.12 (B4)
unnamed: U15.3 (D), U23.13 (B3)
unnamed: U16.2 (R), U25.12 (B4)
unnamed: U16.3 (D), U25.13 (B3)
unnamed: U17.2 (R), U21.10 (B6)
unnamed: U17.3 (D), U21.11 (B5)
unnamed: U18.2 (R), U22.14 (B2)
unnamed: U18.3 (D), U22.16 (B1)
unnamed: U19.2 (R), U23.10 (B6)
unnamed: U19.3 (D), U23.11 (B5)
unnamed: U20.2 (R), U24.14 (B2)
unnamed: U20.3 (D), U24.16 (B1)
unnamed: U4.2 (R), U21.14 (B2)
unnamed: U4.3 (D), U21.16 (B1)
unnamed: U5.2 (R), U22.10 (B6)
unnamed: U5.3 (D), U22.11 (B5)
unnamed: U3.2 (R), U23.14 (B2)
unnamed: U3.3 (D), U23.16 (B1)
unnamed: U6.2 (R), U24.10 (B6)
unnamed: U6.3 (D), U24.11 (B5)
unnamed: U9.2 (R), U25.14 (B2)
unnamed: U9.3 (D), U25.16 (B1)
unnamed: U8.2 (R), U26.10 (B6)
unnamed: U8.3 (D), U26.11 (B5)
unnamed: U7.2 (R), U26.12 (B4)
unnamed: U7.3 (D), U26.13 (B3)
unnamed: U28.2 (~RESET), U29.4 (EN)
